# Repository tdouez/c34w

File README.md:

# c34w

Module wifi pour le TEMPO Linky avec une sortie relais programmable suiva la couleur de la journée.
Indication par leds des coumleurs du jour et du lendemain.

https://fumeebleue.fr/module_tempo/c34w/

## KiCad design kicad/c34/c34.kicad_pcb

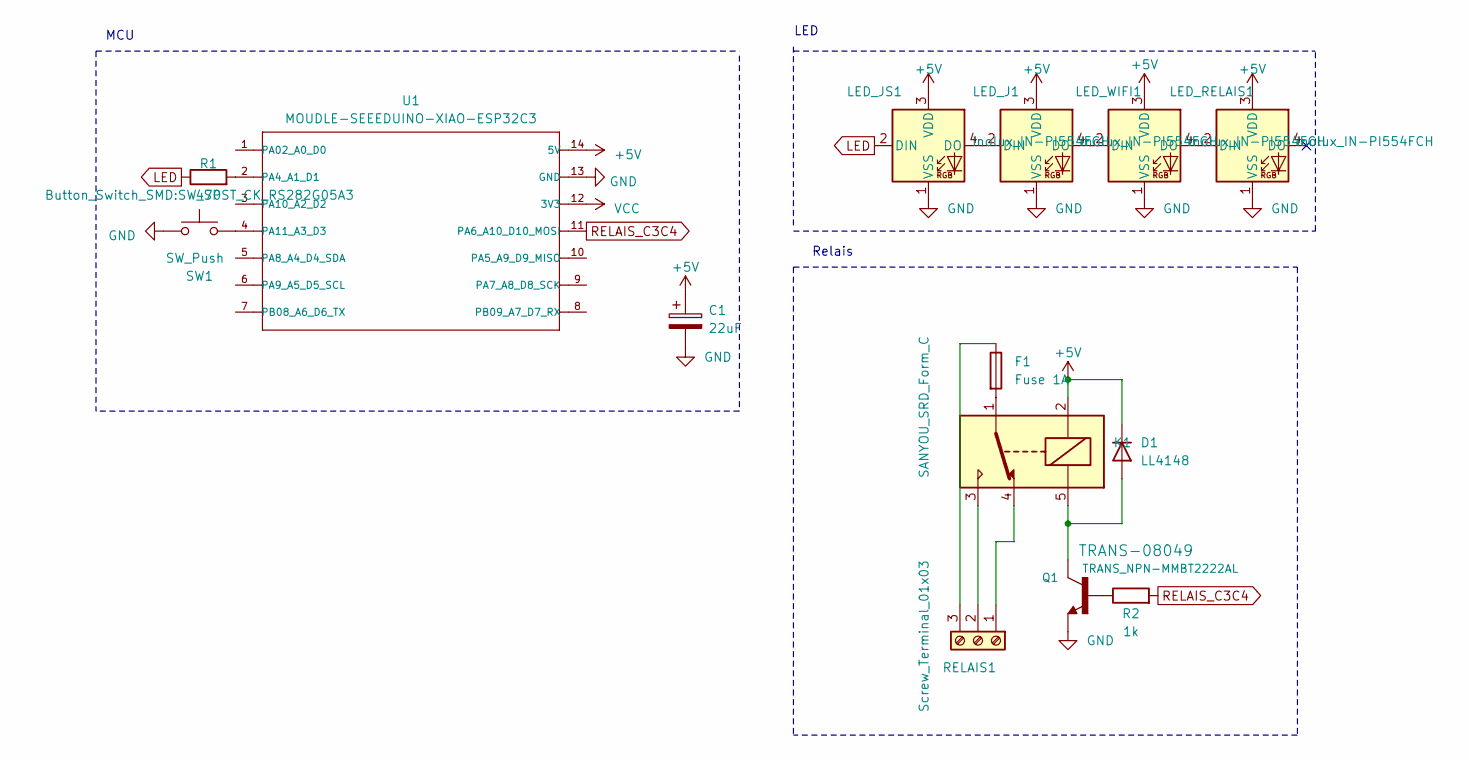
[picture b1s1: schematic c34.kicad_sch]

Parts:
C1: 22uF; C_1210_3225Metric_Pad1.33x2.70mm_HandSolder
D1: LL4148; D_MiniMELF
F1: Fuse 1A; 696310001002
K1: SANYOU_SRD_Form_C; Relay_SPDT_SANYOU_SRD_Series_Form_C
LED_J1: Inolux_IN-PI554FCH; LED_Inolux_IN-PI554FCH_PLCC4_5.0x5.0mm_P3.2mm
LED_JS1: Inolux_IN-PI554FCH; LED_Inolux_IN-PI554FCH_PLCC4_5.0x5.0mm_P3.2mm
LED_RELAIS1: Inolux_IN-PI554FCH; LED_Inolux_IN-PI554FCH_PLCC4_5.0x5.0mm_P3.2mm
LED_WIFI1: Inolux_IN-PI554FCH; LED_Inolux_IN-PI554FCH_PLCC4_5.0x5.0mm_P3.2mm
Q1: TRANS_NPN-MMBT2222AL; SOT-23
R1: 470; R_1206_3216Metric_Pad1.30x1.75mm_HandSolder
R2: 1k; R_1206_3216Metric_Pad1.30x1.75mm_HandSolder
RELAIS1: Screw_Terminal_01x03; TerminalBlock_Altech_AK300-3_P5.00mm
SW1: SW_Push; SW_SPST_CK_RS282G05A3
U1: MOUDLE-SEEEDUINO-XIAO-ESP32C3; MOUDLE14P-SMD-2.54-21X17.8MM

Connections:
+5V: C1.1, D1.1 (K), K1.2, LED_J1.3 (VDD), LED_JS1.3 (VDD), LED_RELAIS1.3 (VDD), LED_WIFI1.3 (VDD), U1.14 (5V)
GND: C1.2, LED_J1.1 (VSS), LED_JS1.1 (VSS), LED_RELAIS1.1 (VSS), LED_WIFI1.1 (VSS), Q1.2 (E), SW1.1, U1.13 (GND)
LED: LED_JS1.2 (DIN), R1.1
unnamed: D1.2 (A), K1.5, Q1.3 (C)
unnamed: F1.2, K1.1
unnamed: LED_J1.2 (DIN), LED_JS1.4 (DO)
unnamed: LED_J1.4 (DO), LED_WIFI1.2 (DIN)
unnamed: LED_RELAIS1.2 (DIN), LED_WIFI1.4 (DO)
unnamed: Q1.1 (B), R2.1
unnamed: K1.4, RELAIS1.1
unnamed: K1.3, RELAIS1.2
unnamed: F1.1, RELAIS1.3
unnamed: R1.2, U1.2 (PA4_A1_D1)
unnamed: SW1.2, U1.4 (PA11_A3_D3)
RELAIS_C3C4: R2.2, U1.11 (PA6_A10_D10_MOSI)
VCC: U1.12 (3V3)

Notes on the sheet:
MCU
Relais
LED

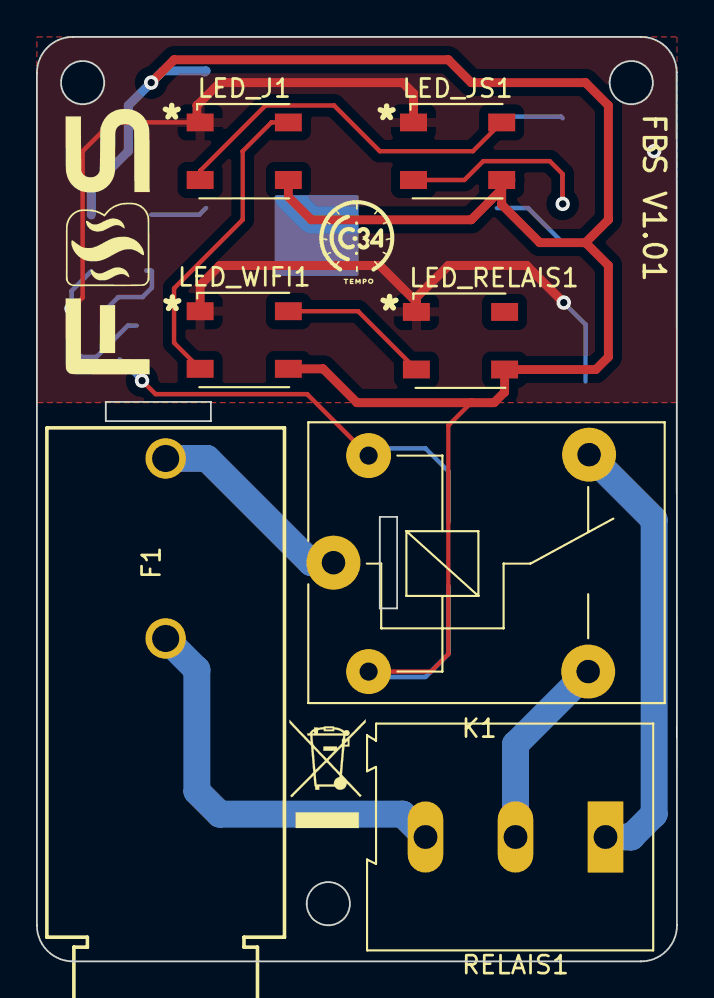
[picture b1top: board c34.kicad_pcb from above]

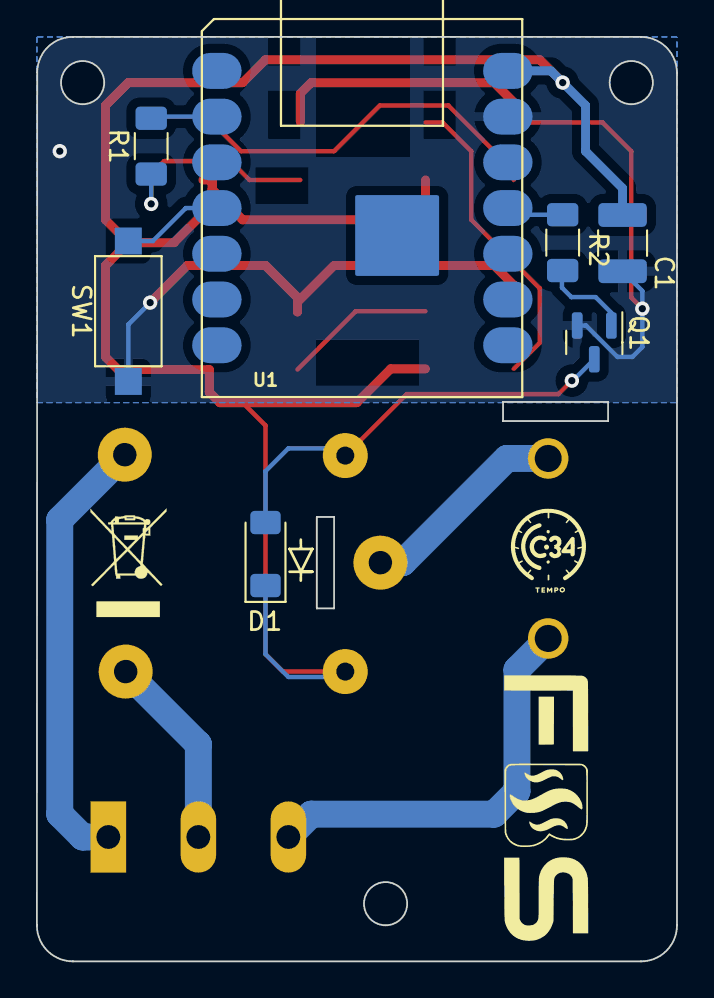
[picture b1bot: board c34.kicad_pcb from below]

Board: 2 copper layers, 35.6 x 51.4 mm, 14 parts (7 on the bottom side), 15 nets.

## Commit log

2024-02-12 V1.1.0
    Mise à jour TEMPO toutes les 15 minutes au lieu de toutes les heures
2024-02-26 v1.2.0
    Correction sur les heures HP et HC inversées
    Passage mise à jour toules les 5 minutes.
    Ajout clignotement jour en HP
2024-02-26 v1.2.0
    maj kicad
2024-02-26 v1.2.0 bin
    Binaires v1.2.0
2024-03-08 v1.2.1
    Ajout test leds au démarrage
2024-03-11 v1.2.1
    Ajout test leds et relais au démarrage
2024-05-29 v1.2.2
    Gestion heure été/hiver
2024-09-05 1.3.0
    Changement de serveur pour la récupération de la couleur TEMPO
2024-09-27 v1.3.1
    Intégration pages web en zone PROGMEM et modif pcb 1.1
